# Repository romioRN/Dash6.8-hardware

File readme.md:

stm32f4

8MB RAM

flash

ESP32 S3 wifi calibration page

ATGM336H GPS with on-board battery

wifi name "service", password 12345678, connect to 192.167.4.1

2 layer PCB

single side assembly

nextPCB

# hardware

* GPS antenna 5v "GPS Antenna SMA Connector Car Mini GPS Receiver Antenna 3 Meters Cable Car GPS Antenna Receiver for Car Navigation Camera Player"

* Пигтейл SMA female - MHF4 адаптер переходник для подключения внешней антенны Best Seller

* ribbon cable FFC FPC 40 pin,Reverse Direction,5cm 0.5mm

* threaded inserts M2xL4xOD3.2

* m2 din912 

# pinout

* pin 6 CANH

* pin 8 GND

* 10 CANL

* pin 12 12v

# Firmware

https://github.com/romioRN/Dash6.8-firmware

precompiled F4 binaries at https://github.com/romioRN/Dash6.8-firmware/tree/main/Firmware/Debug

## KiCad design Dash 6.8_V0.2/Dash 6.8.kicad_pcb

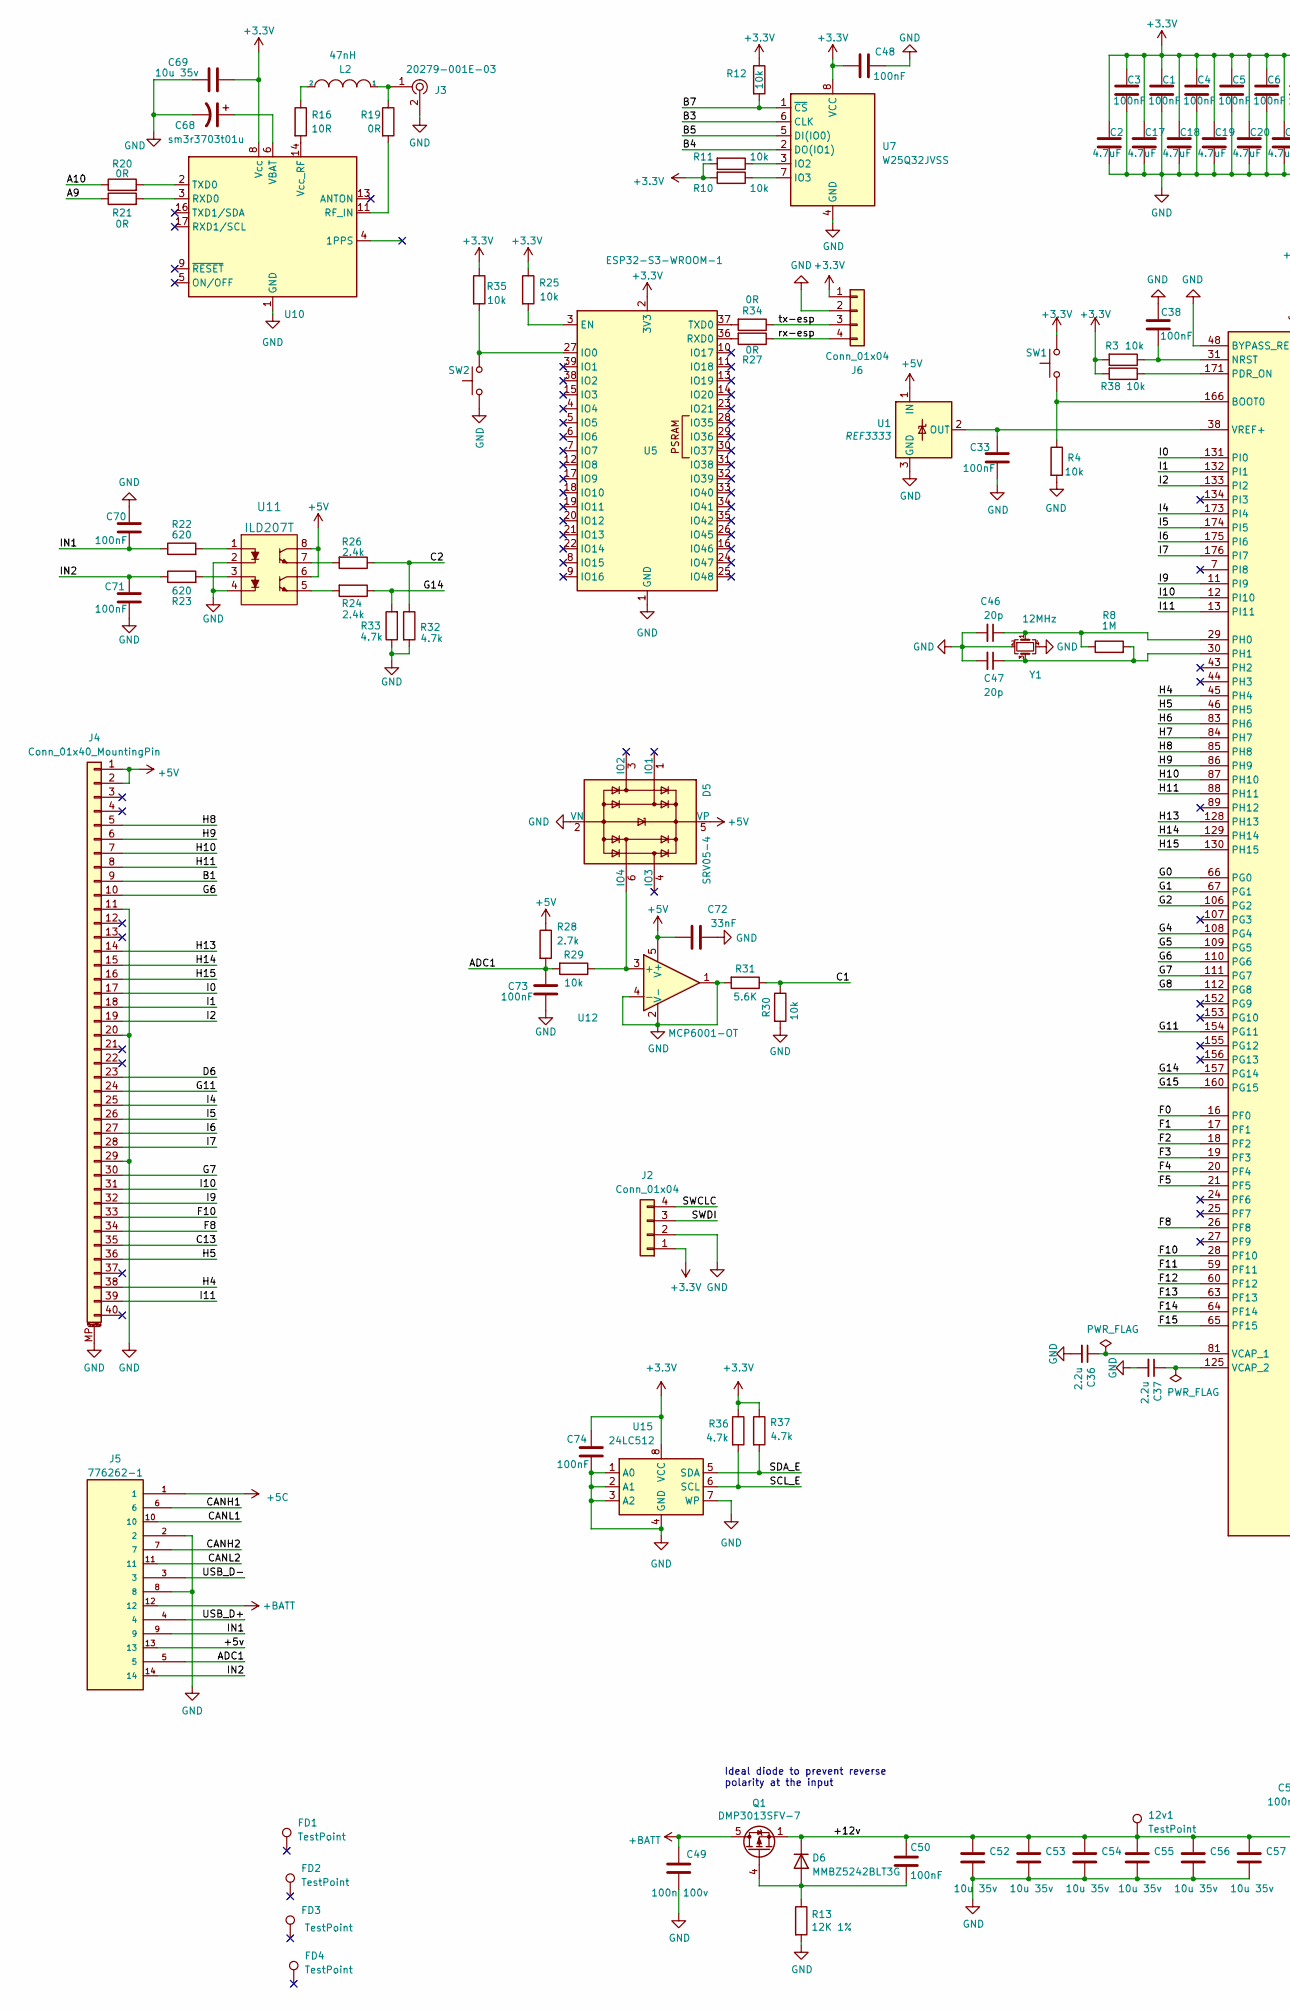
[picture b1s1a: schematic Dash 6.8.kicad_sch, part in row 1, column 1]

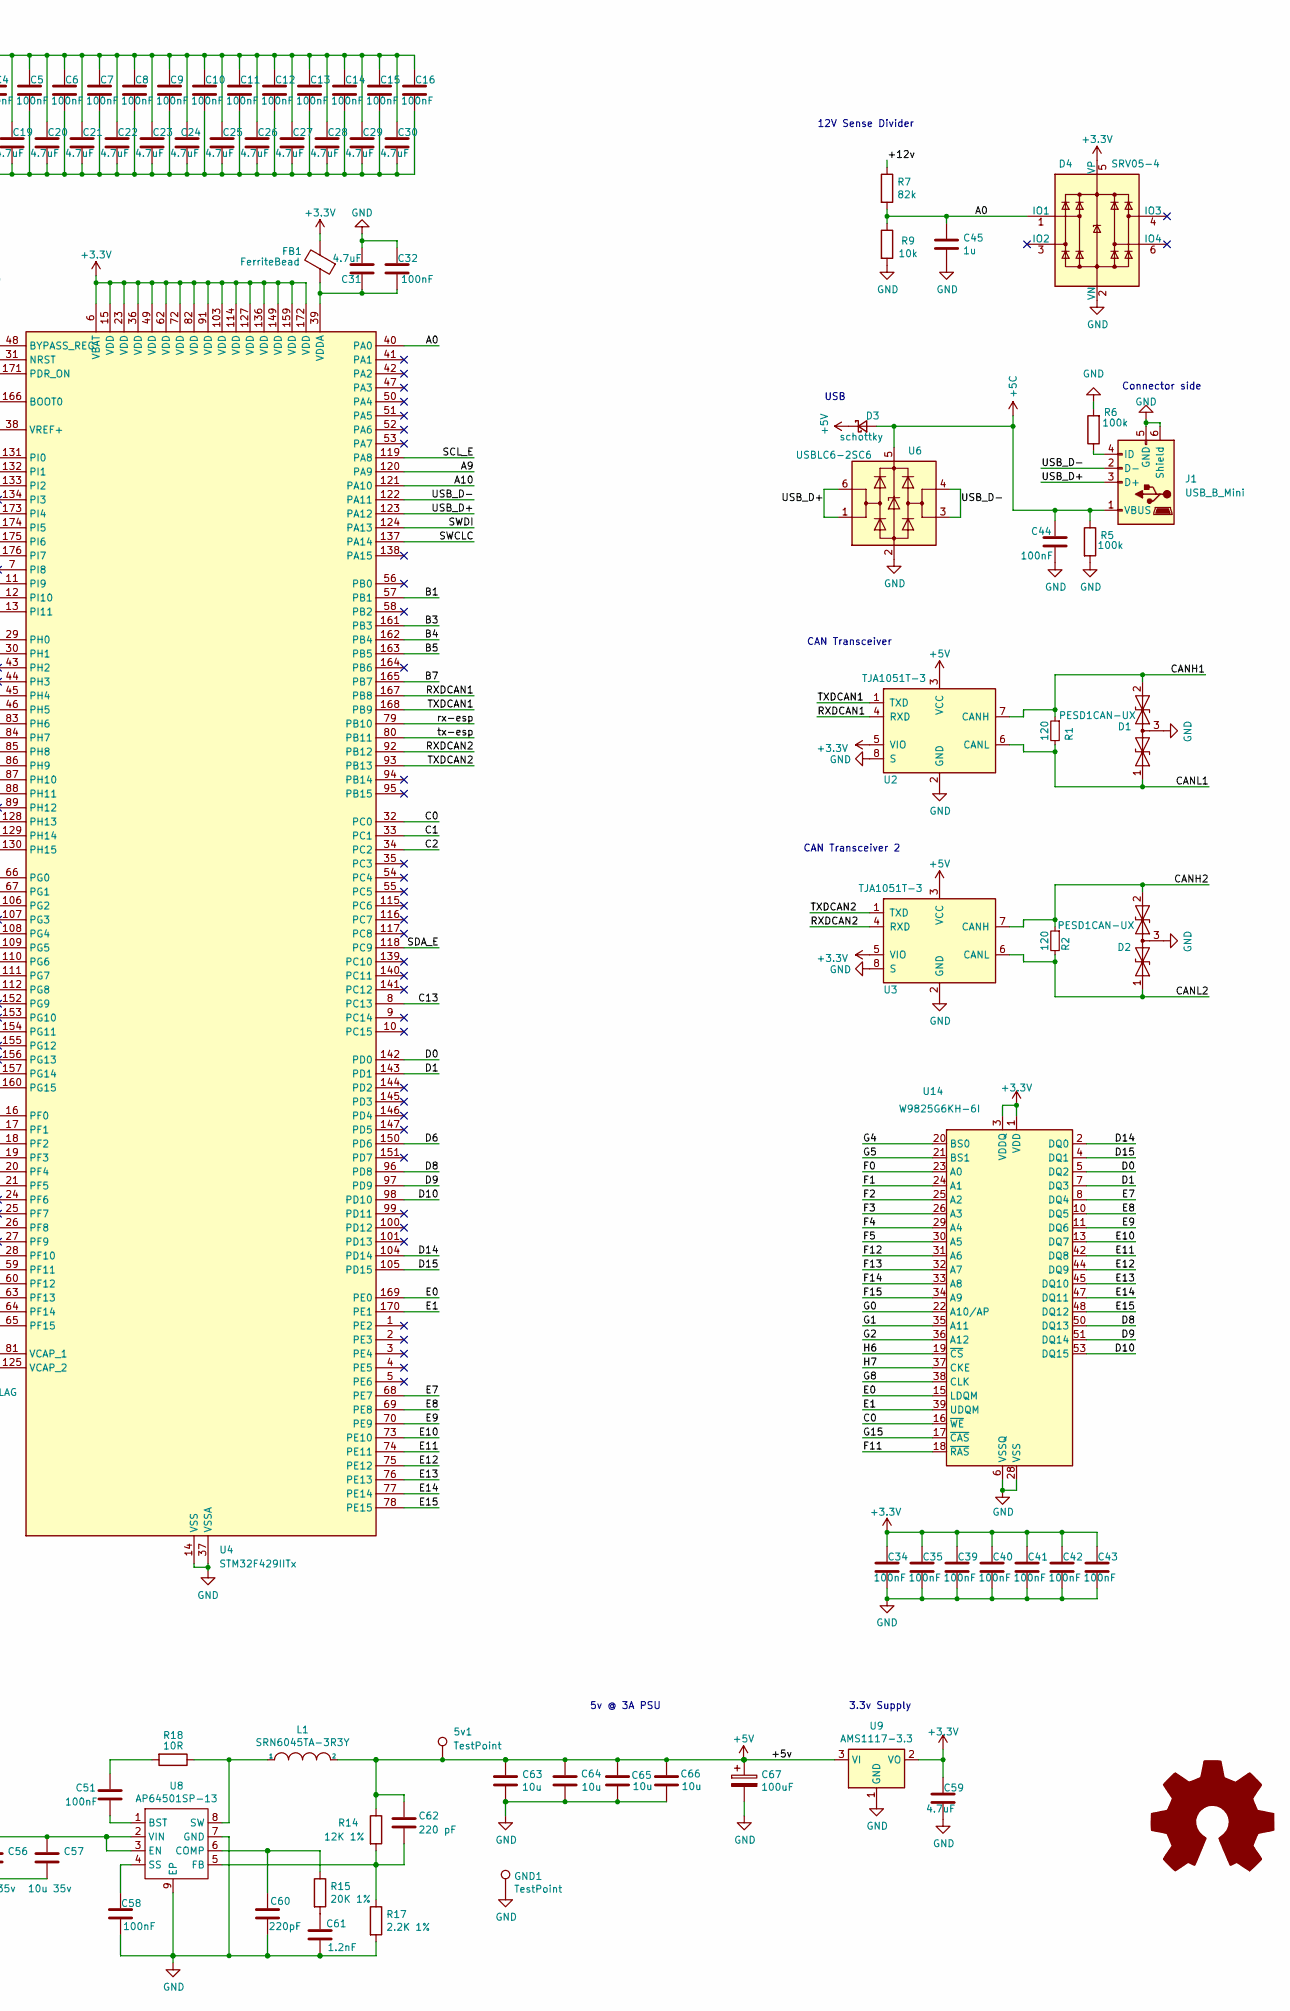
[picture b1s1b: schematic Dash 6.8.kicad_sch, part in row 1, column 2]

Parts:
5v1, 12v1: TestPoint; TestPoint_Pad_D1.5mm
C1, C3, C4, C5, C6, C7, C8, C9, C10, C11, C12, C13, C14, C15, C16, C32, C33, C34, C35, C38, C39, C40, C41, C42, C43, C44, C48, C50, C51, C58, C70, C71, C73, C74: 100nF; C_0603_1608Metric; Part CC0603KRX7R9BB104
C2, C17, C18, C19, C20, C21, C22, C23, C24, C25, C26, C27, C28, C29, C30, C31, C59: 4.7uF; C_0603_1608Metric; Part CL10A475KO8NNNC
C36, C37: 2.2u; C_0603_1608Metric; Part CL10A225KO8NNNC; LCSC C23630
C45: 1u; C_0603_1608Metric; Part CL10A105KB8NNNC; LCSC C15849
C46, C47: 20p; C_0603_1608Metric; Part GRM1885C1H200JA01D
C49: 100n 100v; C_0603_1608Metric; Part CC0603KRX7R0BB104
C52, C53, C54, C55, C56, C57, C69: 10u 35v; C_0805_2012Metric; Part GRM21BC8YA106KE11L
C60: 220pF; C_0603_1608Metric; Part CC0603KRX7R0BB221
C61: 1.2nF; C_0603_1608Metric; Part CC0603KRX7R9BB122
C62: 220 pF; C_0603_1608Metric; Part CC0603KRX7R0BB221
C63, C64, C65, C66: 10u; C_0805_2012Metric; Part GRM21BR71A106KA73L
C67: 100uF; CP_EIA-7343-31_Kemet-D; Part 667-EEF-CX0J101R
C68: sm3r3703t01u; SM3R3703T01U; Part sm3r3703t01u
C72: 33nF; C_0603_1608Metric; Part CL10B333KB8NNNC
D1, D2: PESD1CAN-UX; SOT-323_SC-70; Part PESD1CAN-UX; LCSC C152727
D3: schottky; D_SOD-123; Part B5819W SL; LCSC C8598
D4, D5: SRV05-4; SOT-23-6; Part SRV05-4-P-T7; LCSC C85364
D6: MMBZ5242BLT3G; SOT-23; Part MMBZ5242BLT3G
FB1: FerriteBead; L_0603_1608Metric; Part BLM18PG471SN1D
FD1, FD2, FD3, FD4: TestPoint; Fiducial_0.5mm_Mask1.5mm
GND1: TestPoint; TestPoint_Pad_2.0x2.0mm
J1: USB_B_Mini; USB_Mini-B_Tensility_54-00023_Vertical_CircularHoles; Part 920-462A2021Y10101
J2, J6: Conn_01x04; PinHeader_1x04_P2.54mm_Vertical
J3: 20279-001E-03; U.FL_Molex_MCRF_73412-0110_Vertical; Part 20279-001E-03
J4: Conn_01x40_MountingPin; F-FPC0M40P-C310; Part F-FPC0M40P-C310
J5: 776262-1; TE_776262-1; PARTREV A8
L1: SRN6045TA-3R3Y; L_Bourns_SRN6045TA; Part SRN6045TA-3R3Y
L2: 47nH; L_0603_1608Metric; Part LQW18AN47NG00D
Q1: DMP3013SFV-7; Diodes_PowerDI3333-8; Part DMP3013SFV-7
R1, R2: 120; R_0603_1608Metric; Part RC0603JR-07120RL; LCSC C22787
R3, R4, R9, R10, R11, R12, R25, R29, R30, R35, R38: 10k; R_0603_1608Metric; Part CRCW060310K0FKEAC
R5, R6: 100k; R_0603_1608Metric; Part RC0603FR-07100KL; LCSC_ext 0
R7: 82k; R_0603_1608Metric; Part RC0603JR-0782KL; LCSC_ext 0
R8: 1M; R_0603_1608Metric; Part RT0603BRD071ML
R13, R14: 12K 1%; R_0603_1608Metric; Part RC0603FR-0712KL
R15: 20K 1%; R_0603_1608Metric; Part RC0603FR-0720KL
R16, R18: 10R; R_0603_1608Metric; Part CRCW060310R0FKEA
R17: 2.2K 1%; R_0603_1608Metric; Part RC0603FR-072K2L
R19, R20, R21, R27, R34: 0R; R_0603_1608Metric; Part RC0603JR-070RL
R22, R23: 620; R_0603_1608Metric; Part RC0603JR-07620RL
R24, R26: 2.4k; R_0603_1608Metric; Part RC0603FR-072K4L
R28: 2.7k; R_0603_1608Metric; Part RC0603JR-072K7L
R31: 5.6K; R_0603_1608Metric; Part RT0603BRD075K62L
R32, R33, R36, R37: 4.7k; R_0603_1608Metric; Part RT0603BRD074K7L
SW1, SW2: SW_Push; SW_SPST_EVQQ2; Part TS-1187A-C-E-B; LCSC C318887
U1: REF3333; SOT-23; Part REF3333AIDBZR; LCSC C130016
U2, U3: TJA1051T-3; SOIC-8_3.9x4.9mm_P1.27mm; Part TJA1051T/3/1J; LCSC C38695
U4: STM32F429IITx; LQFP-176_24x24mm_P0.5mm; Part STM32F429IIT6
U5: ESP32-S3-WROOM-1; Part ESP32-S3-WROOM-1-N16R8
U6: USBLC6-2SC6; SOT-23-6; Part USBLC6-2; LCSC C7519
U7: W25Q32JVSS; SOIC-8_5.23x5.23mm_P1.27mm; Part W25Q32JVSSIQ
U8: AP64501SP-13; SOIC-8-1EP_3.9x4.9mm_P1.27mm_EP2.95x4.9mm_Mask2.71x3.4mm_Th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; Part AP64501SP-13
U9: AMS1117-3.3; SOT-223-3_TabPin2; Part AMS1117-3.3; LCSC_ext 0
U10: SIM28ML; Part atgm336h-5n71
U11: ILD207T; SOIC-8_3.9x4.9mm_P1.27mm; Part ILD207T; Digi-Key_PN 751-1310-1-ND
U12: MCP6001-OT; SOT-23-5; Part MCP6001T-I/OT
U14: W9825G6KH-6I; TSOP-II-54_22.2x10.16mm_P0.8mm; Part W9825G6KH-6I
U15: 24LC512; SOIC-8_3.9x4.9mm_P1.27mm; Part M24512-RMN6TP
Y1: 12MHz; Crystal_SMD_3225-4Pin_3.2x2.5mm; Part X322512MOB4SI

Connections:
+3.3V: C1.1, C2.1, C3.1, C4.1, C5.1, C6.1, C7.1, C8.1, C9.1, C10.1, C11.1, C12.1, C13.1, C14.1, C15.1, C16.1, C17.1, C18.1, C19.1, C20.1, C21.1, C22.1, C23.1, C24.1, C25.1, C26.1, C27.1, C28.1, C29.1, C30.1, C34.1, C35.1, C39.1, C40.1, C41.1, C42.1, C43.1, C48.1, C59.1, C69.2, C74.1, D4.5 (VP), FB1.2, J2.1, J6.1, R3.2, R10.2, R11.2, R12.1, R25.1, R35.1, R36.1, R37.1, R38.2, SW1.2, U2.5 (VIO), U3.5 (VIO), U4.6 (VBAT), U4.15 (VDD), U4.23 (VDD), U4.36 (VDD), U4.49 (VDD), U4.62 (VDD), U4.72 (VDD), U4.82 (VDD), U4.91 (VDD), U4.103 (VDD), U4.114 (VDD), U4.127 (VDD), U4.136 (VDD), U4.149 (VDD), U4.159 (VDD), U4.172 (VDD), U5.2 (3V3), U7.8 (VCC), U9.2 (VO), U10.8 (Vcc), U14.1 (VDD), U14.3 (VDDQ), U14.9 (VDDQ), U14.14 (VDD), U14.27 (VDD), U14.43 (VDDQ), U14.49 (VDDQ), U15.8 (VCC)
+5C: C44.1, D3.2 (A), J1.1 (VBUS), J5.1, R5.1, U6.5 (VBUS)
+5V: 5v1.1, C62.1, C63.1, C64.1, C65.1, C66.1, C67.1, C72.2, D3.1 (K), D5.5 (VP), J4.1, J4.2, J5.13, L1.2, R14.1, R28.1, U1.1 (IN), U2.3 (VCC), U3.3 (VCC), U9.3 (VI), U11.6, U11.8, U12.5 (V+)
+BATT: C49.1, J5.12, Q1.5 (D)
/+12v: 12v1.1, C50.1, C52.1, C53.1, C54.1, C55.1, C56.1, C57.1, D6.3 (K), Q1.1 (S), Q1.2 (S), Q1.3 (S), R7.1, U8.2 (VIN), U8.3 (EN)
/A0: C45.1, D4.1 (IO1), R7.2, R9.1, U4.40 (PA0)
/A9: R21.1, U4.120 (PA9)
/A10: R20.1, U4.121 (PA10)
/ADC1: C73.1, J5.5, R28.2, R29.2
/B1: J4.9, U4.57 (PB1)
/B3: U4.161 (PB3), U7.6 (CLK)
/B4: U4.162 (PB4), U7.2 (DO(IO1))
/B5: U4.163 (PB5), U7.5 (DI(IO0))
/B7: R12.2, U4.165 (PB7), U7.1 (~CS)
/C0: U4.32 (PC0), U14.16 (~WE)
/C1: R30.1, R31.1, U4.33 (PC1)
/C2: R26.1, R32.1, U4.34 (PC2)
/C13: J4.35, U4.8 (PC13)
/CANH1: D1.2 (A2), J5.6, R1.1, U2.7 (CANH)
/CANH2: D2.2 (A2), J5.7, R2.1, U3.7 (CANH)
/CANL1: D1.1 (A1), J5.10, R1.2, U2.6 (CANL)
/CANL2: D2.1 (A1), J5.11, R2.2, U3.6 (CANL)
/D0: U4.142 (PD0), U14.5 (DQ2)
/D1: U4.143 (PD1), U14.7 (DQ3)
/D6: J4.23, U4.150 (PD6)
/D8: U4.96 (PD8), U14.50 (DQ13)
/D9: U4.97 (PD9), U14.51 (DQ14)
/D10: U4.98 (PD10), U14.53 (DQ15)
/D14: U4.104 (PD14), U14.2 (DQ0)
/D15: U4.105 (PD15), U14.4 (DQ1)
/E0: U4.169 (PE0), U14.15 (LDQM)
/E1: U4.170 (PE1), U14.39 (UDQM)
/E7: U4.68 (PE7), U14.8 (DQ4)
/E8: U4.69 (PE8), U14.10 (DQ5)
/E9: U4.70 (PE9), U14.11 (DQ6)
/E10: U4.73 (PE10), U14.13 (DQ7)
/E11: U4.74 (PE11), U14.42 (DQ8)
/E12: U4.75 (PE12), U14.44 (DQ9)
/E13: U4.76 (PE13), U14.45 (DQ10)
/E14: U4.77 (PE14), U14.47 (DQ11)
/E15: U4.78 (PE15), U14.48 (DQ12)
/F0: U4.16 (PF0), U14.23 (A0)
/F1: U4.17 (PF1), U14.24 (A1)
/F2: U4.18 (PF2), U14.25 (A2)
/F3: U4.19 (PF3), U14.26 (A3)
/F4: U4.20 (PF4), U14.29 (A4)
/F5: U4.21 (PF5), U14.30 (A5)
/F8: J4.34, U4.26 (PF8)
/F10: J4.33, U4.28 (PF10)
/F11: U4.59 (PF11), U14.18 (~RAS)
/F12: U4.60 (PF12), U14.31 (A6)
/F13: U4.63 (PF13), U14.32 (A7)
/F14: U4.64 (PF14), U14.33 (A8)
/F15: U4.65 (PF15), U14.34 (A9)
/G0: U4.66 (PG0), U14.22 (A10/AP)
/G1: U4.67 (PG1), U14.35 (A11)
/G2: U4.106 (PG2), U14.36 (A12)
/G4: U4.108 (PG4), U14.20 (BS0)
/G5: U4.109 (PG5), U14.21 (BS1)
/G6: J4.10, U4.110 (PG6)
/G7: J4.30, U4.111 (PG7)
/G8: U4.112 (PG8), U14.38 (CLK)
/G11: J4.24, U4.154 (PG11)
/G14: R24.1, R33.2, U4.157 (PG14)
/G15: U4.160 (PG15), U14.17 (~CAS)
/H4: J4.38, U4.45 (PH4)
/H5: J4.36, U4.46 (PH5)
/H6: U4.83 (PH6), U14.19 (~CS)
/H7: U4.84 (PH7), U14.37 (CKE)
/H8: J4.5, U4.85 (PH8)
/H9: J4.6, U4.86 (PH9)
/H10: J4.7, U4.87 (PH10)
/H11: J4.8, U4.88 (PH11)
/H13: J4.14, U4.128 (PH13)
/H14: J4.15, U4.129 (PH14)
/H15: J4.16, U4.130 (PH15)
/I0: J4.17, U4.131 (PI0)
/I1: J4.18, U4.132 (PI1)
/I2: J4.19, U4.133 (PI2)
/I4: J4.25, U4.173 (PI4)
/I5: J4.26, U4.174 (PI5)
/I6: J4.27, U4.175 (PI6)
/I7: J4.28, U4.176 (PI7)
/I9: J4.32, U4.11 (PI9)
/I10: J4.31, U4.12 (PI10)
/I11: J4.39, U4.13 (PI11)
/IN1: C70.2, J5.9, R22.1
/IN2: C71.1, J5.14, R23.1
/RXDCAN1: U2.4 (RXD), U4.167 (PB8)
/RXDCAN2: U3.4 (RXD), U4.92 (PB12)
/SCL_E: R36.2, U4.119 (PA8), U15.6 (SCL)
/SDA_E: R37.2, U4.118 (PC9), U15.5 (SDA)
/SWCLC: J2.4, U4.137 (PA14)
/SWDI: J2.3, U4.124 (PA13)
/TXDCAN1: U2.1 (TXD), U4.168 (PB9)
/TXDCAN2: U3.1 (TXD), U4.93 (PB13)
/USB_D+: J1.3 (D+), J5.4, U4.123 (PA12), U6.1 (I/O1), U6.6 (I/O1)
/USB_D-: J1.2 (D-), J5.3, U4.122 (PA11), U6.3 (I/O2), U6.4 (I/O2)
/rx-esp: J6.4, R27.1, U4.79 (PB10)
/tx-esp: J6.3, R34.1, U4.80 (PB11)
GND: C1.2, C2.2, C3.2, C4.2, C5.2, C6.2, C7.2, C8.2, C9.2, C10.2, C11.2, C12.2, C13.2, C14.2, C15.2, C16.2, C17.2, C18.2, C19.2, C20.2, C21.2, C22.2, C23.2, C24.2, C25.2, C26.2, C27.2, C28.2, C29.2, C30.2, C31.2, C32.1, C33.2, C34.2, C35.2, C36.2, C37.2, C38.1, C39.2, C40.2, C41.2, C42.2, C43.2, C44.2, C45.2, C46.2, C47.2, C48.2, C49.2, C52.2, C53.2, C54.2, C55.2, C56.2, C57.2, C58.2, C59.2, C60.2, C61.2, C63.2, C64.2, C65.2, C66.2, C67.2, C68.2, C69.1, C70.1, C71.2, C72.1, C73.2, C74.2, D1.3 (common), D2.3 (common), D4.2 (VN), D5.2 (VN), GND1.1, J1.5 (GND), J1.6 (Shield), J2.2, J3.2, J4.11, J4.20, J4.29, J4.MP (MountPin), J5.2, J5.8, J6.2, R4.2, R5.2, R6.2, R9.2, R13.2, R17.2, R30.2, R31.2, R32.2, R33.1, SW2.1, U1.3 (GND), U2.2 (GND), U2.8 (S), U3.2 (GND), U3.8 (S), U4.14 (VSS), U4.22 (VSS), U4.37 (VSSA), U4.48 (BYPASS_REG), U4.61 (VSS), U4.71 (VSS), U4.90 (VSS), U4.102 (VSS), U4.113 (VSS), U4.126 (VSS), U4.135 (VSS), U4.148 (VSS), U4.158 (VSS), U5.1 (GND), U5.40 (GND), U5.41 (GND), U6.2 (GND), U7.4 (GND), U8.7 (GND), U8.9 (EP), U9.1 (GND), U10.1 (GND), U10.10 (GND), U10.12 (GND), U11.2, U11.4, U12.1, U12.2 (V-), U12.4 (-), U14.6 (VSSQ), U14.12 (VSSQ), U14.28 (VSS), U14.41 (VSS), U14.46 (VSSQ), U14.52 (VSSQ), U14.54 (VSS), U15.1 (A0), U15.2 (A1), U15.3 (A2), U15.4 (GND), U15.7 (WP), Y1.2, Y1.4
unnamed: C51.1, R18.2
unnamed: C61.1, R15.2
unnamed: D5.6 (IO4), R29.1, U12.3 (+)
unnamed: C50.2, D6.1 (A), Q1.4 (G), R13.1
unnamed: J1.4 (ID), R6.1
unnamed: J3.1, L2.1, R19.1
unnamed: L2.2, R16.1
unnamed: R22.2, U11.1
unnamed: R23.2, U11.3
unnamed: R24.2, U11.5
unnamed: R26.2, U11.7
unnamed: C33.1, U1.2 (OUT), U4.38 (VREF+)
unnamed: R4.1, SW1.1, U4.166 (BOOT0)
unnamed: C38.2, R3.1, U4.31 (NRST)
unnamed: R38.1, U4.171 (PDR_ON)
unnamed: C46.1, R8.1, U4.29 (PH0), Y1.1
unnamed: C47.1, R8.2, U4.30 (PH1), Y1.3
unnamed: C36.1, U4.81 (VCAP_1)
unnamed: C37.1, U4.125 (VCAP_2)
unnamed: C31.1, C32.2, FB1.1, U4.39 (VDDA)
unnamed: R25.2, U5.3 (EN)
unnamed: R35.2, SW2.2, U5.27 (IO0)
unnamed: R27.2, U5.36 (RXD0)
unnamed: R34.2, U5.37 (TXD0)
unnamed: R11.1, U7.3 (IO2)
unnamed: R10.1, U7.7 (IO3)
unnamed: C51.2, U8.1 (BST)
unnamed: C60.1, R15.1, U8.6 (COMP)
unnamed: C62.2, R14.2, R17.1, U8.5 (FB)
unnamed: C58.1, U8.4 (SS)
unnamed: L1.1, R18.1, U8.8 (SW)
unnamed: R19.2, U10.11 (RF_IN)
unnamed: R21.2, U10.3 (RXD0)
unnamed: R20.2, U10.2 (TXD0)
unnamed: C68.1, U10.6 (VBAT)
unnamed: R16.2, U10.14 (Vcc_RF)

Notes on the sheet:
Ideal diode to prevent reverse polarity at the input
USB
3.3v Supply
12V Sense Divider
CAN Transceiver 2
5v @ 3A PSU
Connector side
CAN Transceiver

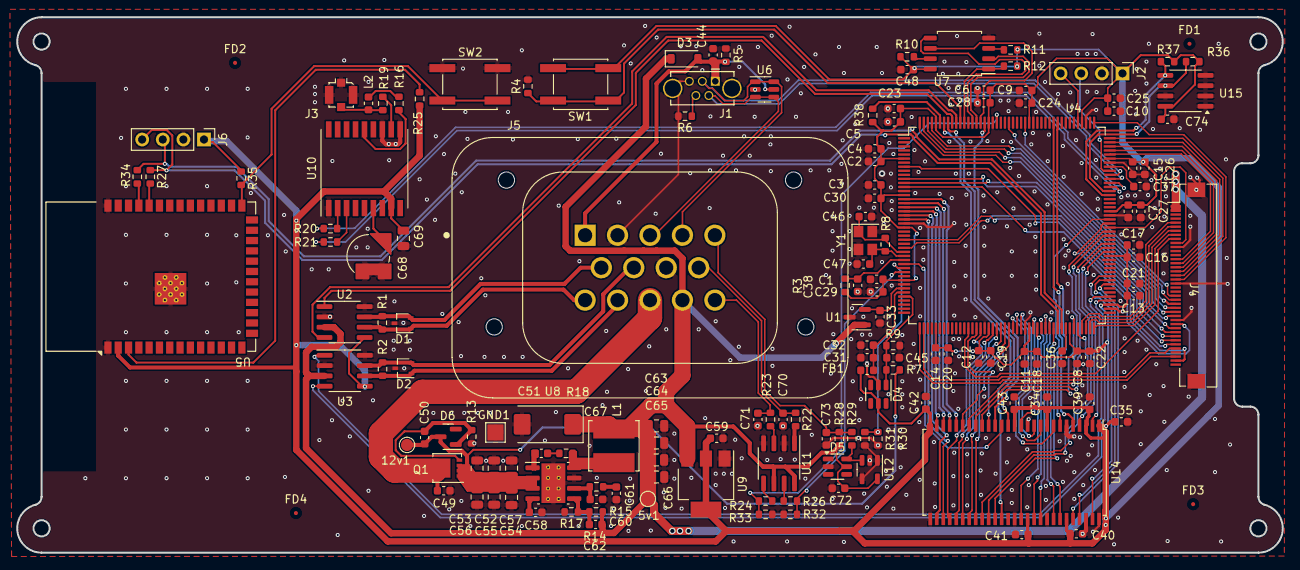
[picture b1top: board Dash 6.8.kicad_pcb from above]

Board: 2 copper layers, 156.0 x 66.0 mm, 152 parts (0 on the bottom side), 137 nets.

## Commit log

2025-05-22 добовление ESP32 обновлен корпус
2025-06-23 новая версия платы
2025-08-10 рама платы
2025-08-21 info
2025-08-21 removing backups
2025-08-21 typo BOM not boom
2025-08-21 looks like temp files
2025-08-21 enclosure files
2025-08-21 wifi name "service", password 12345678, connect at 192.167.4.1
2025-08-21 hw details
2025-09-16 уброно лишнее исправлены название паопк
2025-09-16 исправление платы V01
2025-09-16 исправление платы V02
2025-10-01 ignore-idea
2025-10-01 enclosure fix and clarification
2025-10-01 fw repo name
